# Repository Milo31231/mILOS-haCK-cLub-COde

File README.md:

# Sound Voltex Macro Pad

A low-cost, open-source **Sound Voltex-style (SDVX) rhythm game controller** built around the Seeed XIAO RP2040. It has 7 buttons and 2 rotary encoders on a custom PCB designed in KiCad, with a 3D-modeled enclosure designed in Autodesk Fusion 360.

Built for **[Hack Club](https://hackclub.com) Stardance**.

## Why I'm building this

Commercial SDVX-style controllers can be expensive. The goal of this project is a cheaper, more accessible controller that anyone in the community can build, modify, and learn from.

## Features

- **7 MX-style mechanical switches** in an SDVX-inspired layout
- **2 rotary encoders** for the knobs
- **Seeed XIAO RP2040** microcontroller with a USB-C connection
- **Custom PCB** with schematic and board layout designed in KiCad
- **3D-printable enclosure** modeled in Fusion 360, with a USB-C cutout and corner mounting holes
- **Firmware:** QMK (in progress)

## Hardware

| Qty | Part |
|----:|------|
| 1 | Seeed XIAO RP2040 |
| 7 | MX-style mechanical switches |
| 2 | Rotary encoders |
| 7 | Keycaps |
| 2 | Knobs |
| 1 | Custom PCB (KiCad files in this repo) |
| 1 | 3D-printed enclosure |

## Pin mapping

| Input | XIAO pin |
|-------|----------|
| SW1 | D0 |
| SW2 | D1 |
| SW3 | D2 |
| SW4 | D3 |
| SW5 | D4 |
| SW6 | D5 |
| SW7 | D6 |
| Encoder 1 (A / B) | D7 / D8 |
| Encoder 2 (A / B) | D9 / D10 |

All switches share a common ground. Each one is wired directly to its own GPIO pin.

## Design

### Schematic

### PCB layout

Routed board in KiCad:

3D views of the board with components:

### Enclosure

The enclosure is modeled around the board so that the XIAO's USB-C port lines up with a cutout in the side wall.

### Early prototype

The first version was a 3-key test board used to check footprints and case fit before moving to the full layout.

## Status

- [x] Schematic
- [x] PCB layout and routing
- [x] 3D enclosure model
- [ ] Firmware (QMK), in progress
- [ ] Order PCB and assemble
- [ ] Print enclosure and test

## Tools

- **KiCad:** schematic capture and PCB design
- **Autodesk Fusion 360:** enclosure and 3D modeling
- **QMK** (via QMK MSYS): firmware
- **Lychee Slicer:** preparing the enclosure for resin 3D printing

## About

Designed by **Milo Sa**, a first-year Computer Engineering student at Washington State University.

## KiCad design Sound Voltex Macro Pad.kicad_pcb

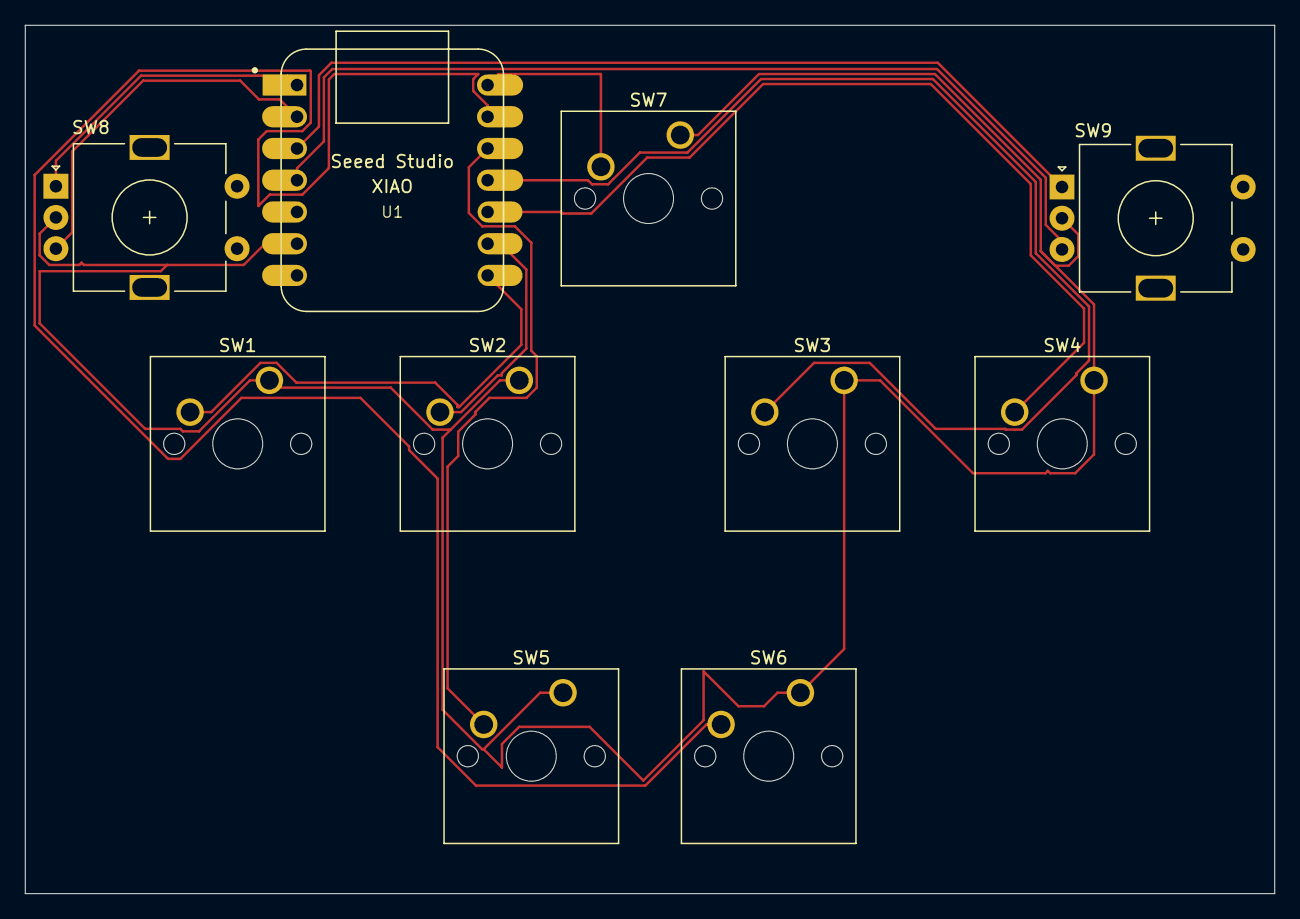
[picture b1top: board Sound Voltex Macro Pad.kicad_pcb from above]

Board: 2 copper layers, 100.0 x 69.5 mm, 10 parts (0 on the bottom side), 12 nets.

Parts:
SW1, SW2, SW3, SW4, SW5, SW6, SW7: SW_Push; SW_Cherry_MX_1.00u_PCB
SW8, SW9: RotaryEncoder; RotaryEncoder_Alps_EC11E-Switch_Vertical_H20mm
U1: MOUDLE-SEEEDUINO-XIAO; XIAO-Generic-Hybrid-14P-2.54-21X17.8MM

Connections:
/RE 1: SW9.A, U1.3 (PA10_A2_D2)
/RE 2: SW9.B, U1.4 (PA11_A3_D3)
/RE 3: SW8.A, U1.1 (PA02_A0_D0)
/RE 4: SW8.B, U1.2 (PA4_A1_D1)
GND: SW1.1, SW2.1, SW3.1, SW4.1, SW5.1, SW6.1, SW7.1, SW8.C, SW9.C, U1.6 (PA9_A5_D5_SCL)
unnamed: SW5.2, U1.12 (3V3)
unnamed: SW7.2, U1.14 (5V)
unnamed: SW6.2, U1.13 (GND)
unnamed: SW4.2, U1.10 (PA5_A9_D9_MISO)
unnamed: SW3.2, U1.11 (PA6_A10_D10_MOSI)
unnamed: SW2.2, U1.9 (PA7_A8_D8_SCK)
unnamed: SW1.2, U1.8 (PB09_A7_D7_RX)
